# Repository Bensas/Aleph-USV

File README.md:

# [WIP] Aleph (Unmanned Surface Vehicle)
This repo contains code for the on-board software, as well as electronic and mechanical designs for Aleph, the main vehicle in Project Borges, ultimately tasked to to an autonomous, solar-powered atlantic crossing.

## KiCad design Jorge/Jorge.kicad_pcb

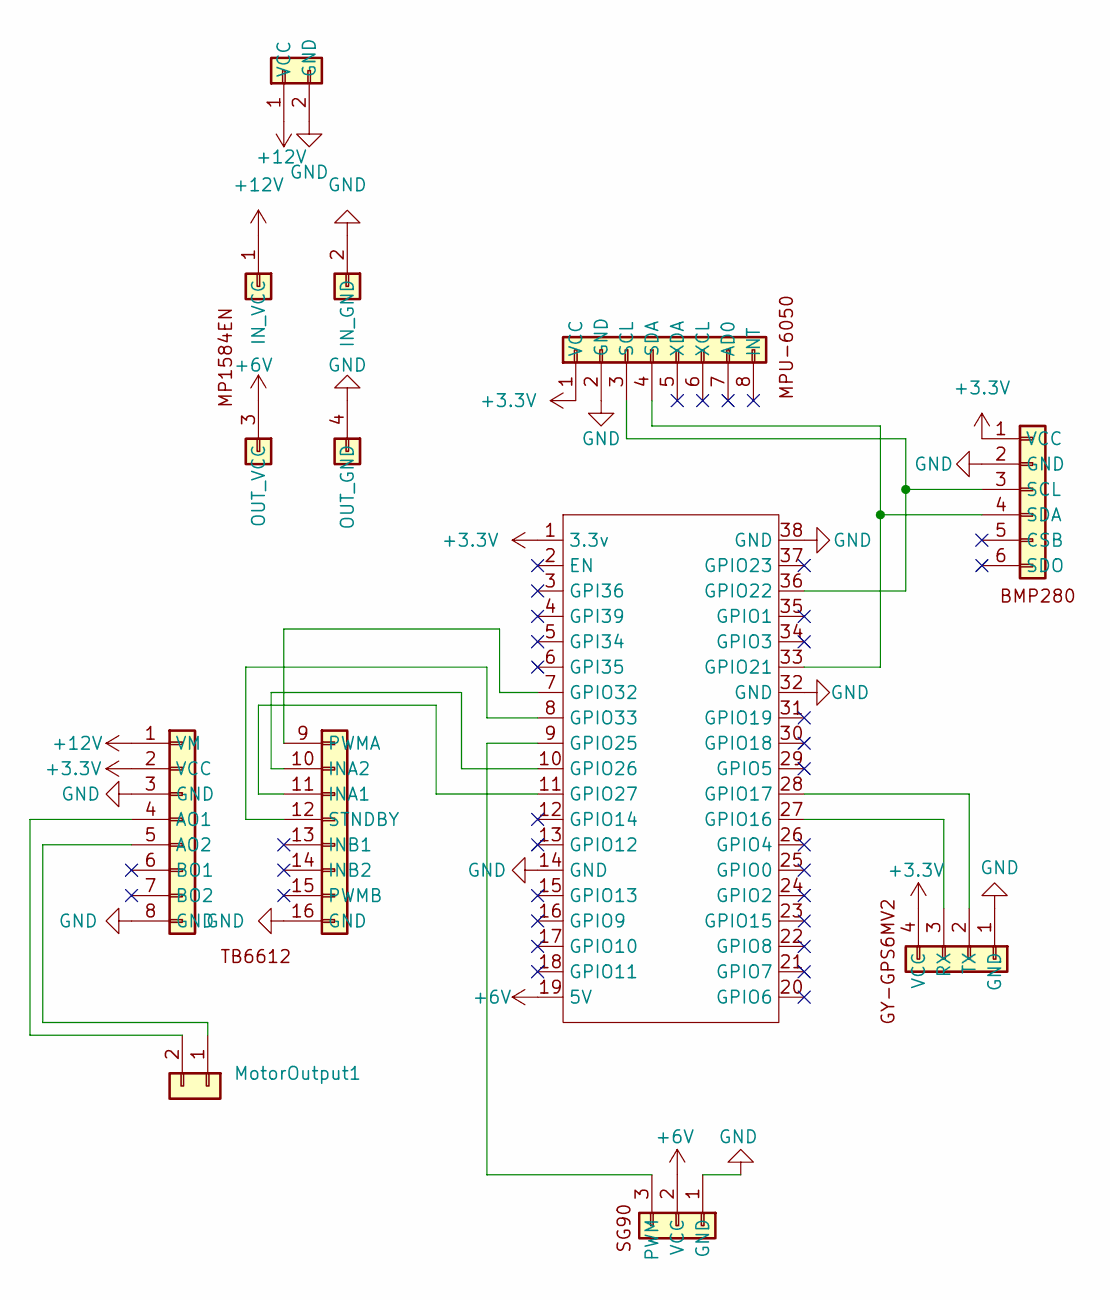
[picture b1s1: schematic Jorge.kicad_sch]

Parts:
BMP1: BME280_breakout_footprint
DC_Input1: BarrelJack_Horizontal
GY-GPS6MV1: GY-GPS6MV2_footprint
MP1584EN1: MP1584_breakout_footprint
MPU-1: MPU6050_breakout_footprint
MotorOutput1: Motor Output; TerminalBlock_Phoenix_MKDS-1,5-2-5.08_1x02_P5.08mm_Horizont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
SG1: PinSocket_1x03_P2.54mm_Vertical
TB1: TB6612_breakout_footprint
U1: ESP32-38pin

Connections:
+3.3V: BMP1.1 (VCC), GY-GPS6MV1.4 (VCC), MPU-1.1 (VCC), TB1.2 (VCC), U1.1 (3.3v)
+6V: MP1584EN1.3 (OUT_VCC), SG1.2 (VCC), U1.19 (5V)
+12V: DC_Input1.1 (VCC), MP1584EN1.1 (IN_VCC), TB1.1 (VM)
GND: BMP1.2 (GND), DC_Input1.2 (GND), GY-GPS6MV1.1 (GND), MP1584EN1.2 (IN_GND), MP1584EN1.4 (OUT_GND), MPU-1.2 (GND), SG1.1 (GND), TB1.3 (GND), TB1.8 (GND), TB1.16 (GND), U1.14 (GND), U1.32 (GND), U1.38 (GND)
unnamed: BMP1.3 (SCL), MPU-1.3 (SCL), U1.36 (GPIO22)
unnamed: BMP1.4 (SDA), MPU-1.4 (SDA), U1.33 (GPIO21)
unnamed: GY-GPS6MV1.3 (RX), U1.27 (GPIO16)
unnamed: GY-GPS6MV1.2 (TX), U1.28 (GPIO17)
unnamed: MotorOutput1.1, TB1.5 (AO2)
unnamed: MotorOutput1.2, TB1.4 (AO1)
unnamed: SG1.3 (PWM), U1.9 (GPIO25)
unnamed: TB1.11 (INA1), U1.11 (GPIO27)
unnamed: TB1.10 (INA2), U1.10 (GPIO26)
unnamed: TB1.9 (PWMA), U1.7 (GPIO32)
unnamed: TB1.12 (STNDBY), U1.8 (GPIO33)

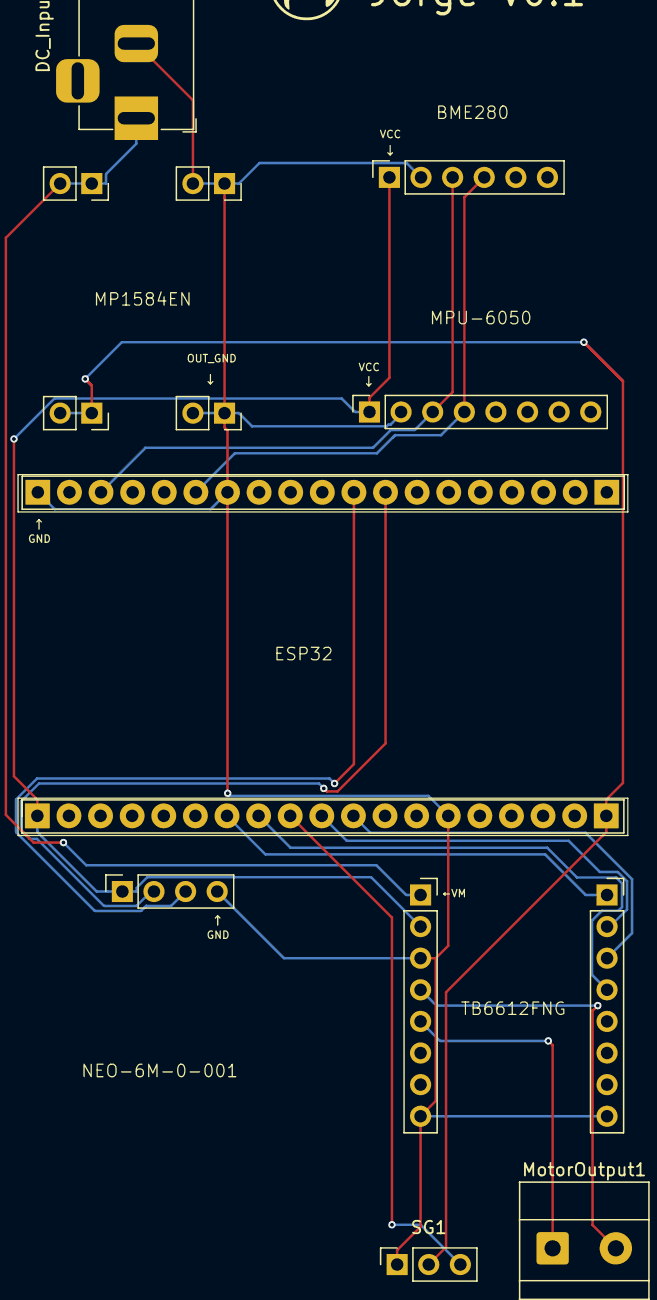
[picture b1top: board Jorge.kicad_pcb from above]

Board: 2 copper layers, 9 parts (0 on the bottom side), 15 nets.

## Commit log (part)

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2025-08-15 Working code for reading from BMP280 and MPU6050 using I2C
2025-08-15 Created SensorModule for sensor communication logic
2025-08-15 Added WebModule to host website for data visualization
2025-08-16 Added support for the GY-GPS6MV2 module
2025-08-16 Changed Wifi SSID, removed comment, changed base pressure (hPa)
2025-08-21 Added ActuatorModule with servo control
2025-08-21 Added first version of Jorge PCB. Only 12v and 3.3v lines are available, so servo does not get enough voltage. Need to iterate.
2025-10-27 Modified PCB to user Battery 12V -> Regulator 6V -> ESP32 regulator 3.3V system
2025-10-27 Use LEDC instead of ESP32Servo.h library for servo control (now working)
2025-10-27 Added motor control. Everything works now, PCB will be sent to print.
2025-10-27 Added Aleph Icon
